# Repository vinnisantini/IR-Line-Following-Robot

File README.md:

# IR Line Following Robot
IR line following robot

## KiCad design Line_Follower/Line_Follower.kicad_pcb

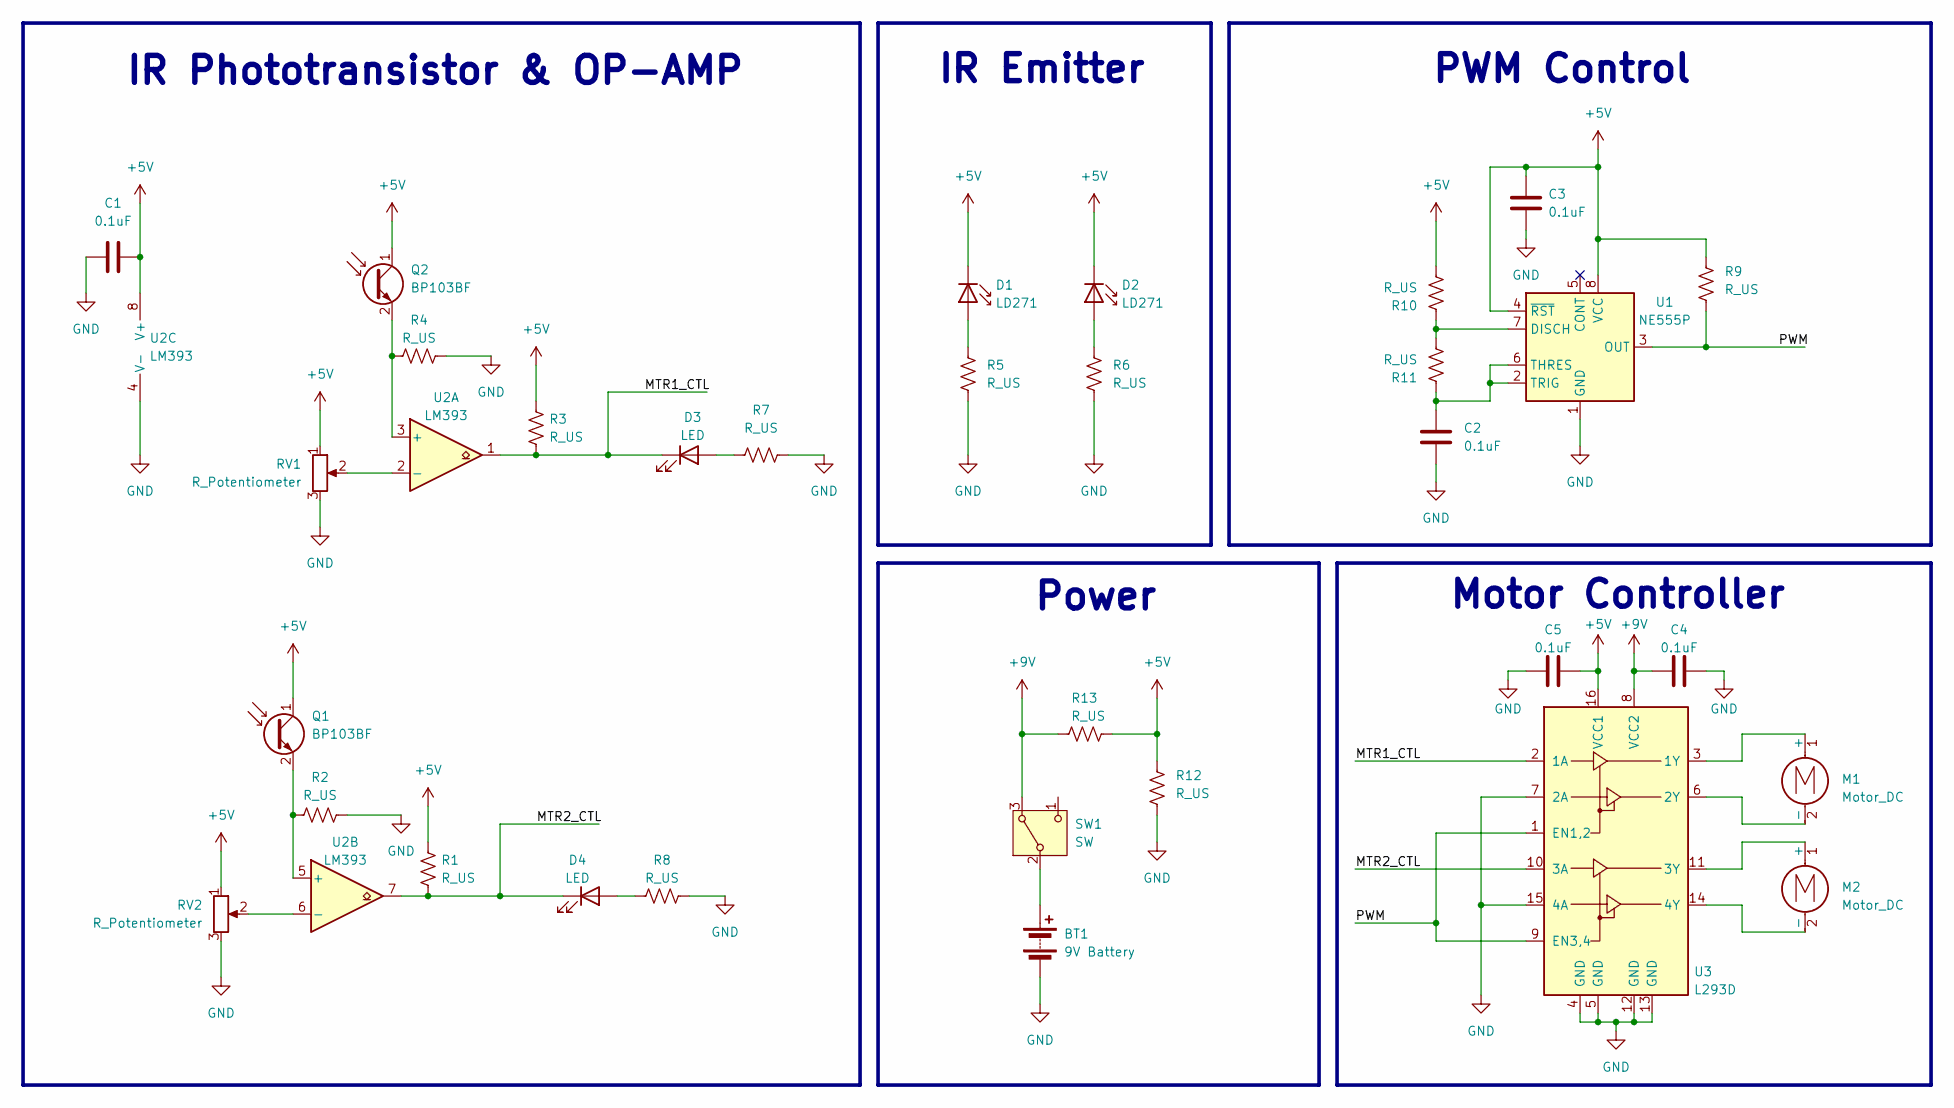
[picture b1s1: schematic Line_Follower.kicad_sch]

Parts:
BT1: 9V Battery; BatteryHolder_MPD_BA9VPC_1xPP3
C1, C2, C3, C4, C5: 0.1uF; CP_Radial_Tantal_D8.0mm_P2.50mm
D1, D2: LD271; LED_D5.0mm_IRGrey
D3, D4: LED; LED_D5.0mm
M1, M2: Motor_DC; PinHeader_2x01_P2.54mm_Vertical
Q1, Q2: BP103BF; LED_D5.0mm_Clear
R1, R2, R3, R4, R5, R6, R7, R8, R9, R10, R11, R12, R13: R_US; R_Axial_DIN0207_L6.3mm_D2.5mm_P10.16mm_Horizontal
RV1, RV2: R_Potentiometer; Potentiometer_Runtron_RM-065_Vertical
SW1: SW; SW_Slide_SPDT_Straight_CK_OS102011MS2Q
U1: NE555P; DIP-8_W7.62mm
U2: LM393; DIP-8_W7.62mm
U3: L293D; DIP-16_W7.62mm

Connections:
+5V: C1.1, C3.2, C5.1, D1.1 (K), D2.1 (K), Q1.1 (C), Q2.1 (C), R1.1, R3.1, R9.2, R10.1, R12.2, R13.1, RV1.1, RV2.1, U1.4 (~RST), U1.8 (VCC), U2.8 (V+), U3.16 (VCC1)
+9V: C4.2, R13.2, SW1.3 (A), U3.8 (VCC2)
/MTR1_CTL: D3.1 (K), R3.2, U2.1, U3.2 (1A)
/MTR2_CTL: D4.1 (K), R1.2, U2.7, U3.10 (3A)
/PWM: R9.1, U1.3 (OUT), U3.1 (EN1,2), U3.9 (EN3,4)
GND: BT1.2 (-), C1.2, C2.1, C3.1, C4.1, C5.2, R2.2, R4.2, R5.2, R6.2, R7.2, R8.2, R12.1, RV1.3, RV2.3, U1.1 (GND), U2.4 (V-), U3.4 (GND), U3.5 (GND), U3.7 (2A), U3.12 (GND), U3.13 (GND), U3.15 (4A)
unnamed: BT1.1 (+), SW1.2 (B)
unnamed: D1.2 (A), R5.1
unnamed: D2.2 (A), R6.1
unnamed: D3.2 (A), R7.1
unnamed: D4.2 (A), R8.1
unnamed: M1.1 (+), U3.3 (1Y)
unnamed: M1.2 (-), U3.6 (2Y)
unnamed: M2.1 (+), U3.11 (3Y)
unnamed: M2.2 (-), U3.14 (4Y)
unnamed: Q1.2 (E), R2.1, U2.5 (+)
unnamed: Q2.2 (E), R4.1, U2.3 (+)
unnamed: R10.2, R11.1, U1.7 (DISCH)
unnamed: C2.2, R11.2, U1.2 (TRIG), U1.6 (THRES)
unnamed: RV1.2, U2.2 (-)
unnamed: RV2.2, U2.6 (-)

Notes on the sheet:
IR Phototransistor & OP-AMP
IR Emitter
Motor Controller
Power
PWM Control

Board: 2 copper layers, 33 parts (0 on the bottom side), 21 nets, no tracks yet.
